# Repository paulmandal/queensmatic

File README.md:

# Queensmatic

This project is a wall-mounted NAS with controllable LED strips attached to its case.

# Requirements

- [Python](https://www.python.org/downloads/)
- [Docker CE](https://www.docker.com/community-edition#/download)
- [Android Studio + SDK](https://developer.android.com/studio/index.html)
- [Arduino](https://www.arduino.cc/en/Main/Software)
- [Eagle](https://www.autodesk.com/products/eagle/free-download)

# Table of Contents

| Directory | Contents |
|---|----|
| QueensmaticLEDController | Android LED controller application with simple color picker and touchscreen LED updating |
| hardware/circuit | Eagle schematics for the LED controller PCB |
| led-controller-uservice | Microservice used for communication between the Android app (or apps) and the LED controller hardware |
| ucontroller | Microcontroller code - receives messages from the API via serial and updates the LED strips |
| pictures | Some pictures of the building process |

# Running the API

```
cd led-controller-uservice
virtualenv venv
source venv/bin/activate
pip install docker-compose
# Update docker-compose.yml with the serial port for your microcontroller board -- under "devices"
docker-compose up
```

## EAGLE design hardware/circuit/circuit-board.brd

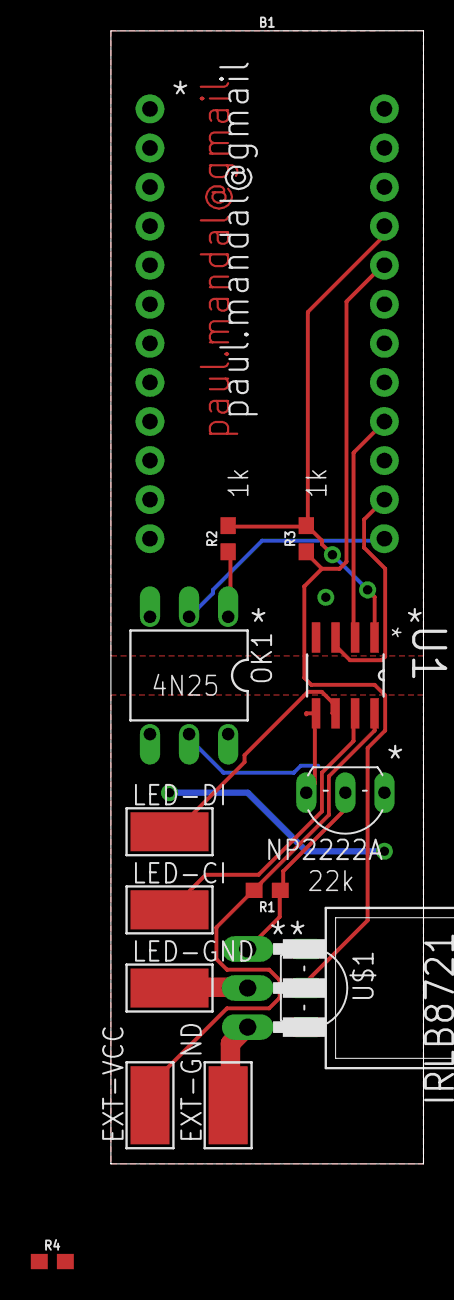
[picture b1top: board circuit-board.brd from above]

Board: 2 copper layers, 20.3 x 73.7 mm, 15 parts (0 on the bottom side), 15 nets.

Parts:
B1: SPARKFUN_PRO_MICRO
EXT-GND: WIREPADSMD5-2,5; 5-2,5
EXT-VCC: WIREPADSMD5-2,5; 5-2,5
IRLB8721: TO220BH
LED-CI: WIREPADSMD5-2,5; 5-2,5
LED-DI: WIREPADSMD5-2,5; 5-2,5
LED-GND: WIREPADSMD5-2,5; 5-2,5
NP2222A: 2N2222; TO92-EBC-OVAL
OK1: 4N25M; DIL06
R1: 22k; 0603
R2, R3: 1k; 0603
R4: 100k; 0603
U1: ADUM1200CRZ; SOIC127P600X175-8N
U$1: LM335AZ; TO92-

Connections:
+5V: EXT-VCC.1, R1.2, U1.8
ADUM-GND2: NP2222A.C, U1.5
GND: B1.3, B1.4, B1.23, U1.4, U$1.1
GNDA: EXT-GND.1, IRLB8721.S, NP2222A.E, OK1.4
unnamed: LED-DI.1, U1.6
unnamed: NP2222A.B, R4.2
unnamed: IRLB8721.D, LED-GND.1
unnamed: OK1.1, R2.1
unnamed: B1.14, U1.3
unnamed: B1.16, U1.2
unnamed: LED-CI.1, U1.7
unnamed: B1.13, OK1.2
PWR-CTRL: IRLB8721.G, OK1.5, R1.1, R4.1
TEMP: B1.20, R3.1, U$1.2
VCC: B1.21, R2.2, R3.2, U1.1

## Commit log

2017-03-11 Added WORKLIST.md to track tasks
2017-03-11 Added some possible improvements to IMPROVEMENTS.md
2017-03-11 Added API definition from SwaggerHub
2017-03-11 Added database definition to docs
2017-03-11 Added .gitignore files
2017-03-11 Added Flask setup, /configuration endpoint with GET, and initial configuration database creation
2017-03-11 Moved configuration database code into its own file, updated .gitignore
2017-03-12 configdb.py - added code to retrieve column names and to store updated configurations
2017-03-12 Added /configuration and /leds endpoints, added ucontroller.py to send update LED commands to the uController, added constants.py, Added /configuration and /leds endpoints for updating the config and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
2017-03-12 Added code to ucontroller.py to set the configuration on the uController, refactored a bit
2017-03-12 Refactore a bunch of names in API code
2017-03-12 Finished API for now, starting on uController code
2017-03-12 Set theme jekyll-theme-midnight
2017-03-12 Fixed an issues with ucontroller.set_config()
2017-03-12 Fixed an issue with update_led()
2017-03-12 Added uController skeleton, taking a break
2017-03-12 Added uController skeleton, added some improvements to improvements list
2017-03-12 Added uController commands documentation
2017-03-12 Added message buffer, handling of config update commands to uController code
2017-03-12 Added code to handle updating LEDs from serial commands, added code to output LED status to serial, added some comments,
2017-03-13 Renamed led_controller.ino to ucontroller.ino
2017-03-13 Added code to update LED strip to uController - need to debug LED protocol
2017-03-14 Changed r/g/b/brightness types to byte, normalized brightness value, fixed issue with headerByte not being reset before each LED loop, fixed issue with headerByte using & instead of |, added some deb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
2017-03-14 Removed debugging code, set up controller to update LED strip whenever configuration is changed
2017-03-14 Removed app->hardware r/g/b/brightness level remapping because most phones and LED strips only support 8-bit color
2017-03-14 Added Android app, created some data model objects
2017-03-15 Fleshed out config activity a bit, taking a break to eat
2017-03-15 Added fetching of configuration from API, set up Flask to listen to any interface
2017-03-15 Added storing of configuration from app->API, added permissions requesting, fixed JSON responses from API
2017-03-15 Moved JSON<->Native translation to ApiTranslator
2017-03-15 Added test button & LED updating to ApiConnection
2017-03-15 Fixed serial communication in Python code
2017-03-16 Started implementing LED drawing screen, added config fetching from API
2017-03-16 Finished setting up UI, setting up LED data structs now
2017-03-16 Basic drawing is in place - need to improve touch handling, right now you have to tap each LED but dragging the color over them would be a lot cooler
2017-03-16 Updated WORKLIST
2017-03-18 Added touch detection to drawing screen, it's in good enough shape for now, time to switch to hardware for a bit..
2017-03-18 Improved error handling in draw screen - user now has the option to re-try fetching the config, or they can cancel and go back to setup
2017-03-21 Added initial circuit diagram with just components
2017-03-21 Added wiring and some resistor values, replaced ISO7221MDR with ADUM1285CRZ because it has the pin arrangement (both inputs on the same side)
2017-03-21 Added temperature sensor to circuit schematic
2017-03-21 Added power pin toggling control to uController code
2017-03-21 Added status request to uController code, updated command docs
2017-03-22 Rerouted wiring for 4N25 optocoupler - signal was being inverted
2017-03-23 Added temperature sensor reading to uController code, added automatic poweroff above 40C
2017-03-23 Updated API definition to include /status endpoint, added GET/PUT, added get_status to API code
2017-03-23 Added PUT to /status endpoint, wired up to P command in uController
2017-03-23 Fixed incorrect pin assignment in LM335AZ in circuit schematic
2017-03-26 Fixed unit in uController code
2017-03-26 Added code to re-update LED strip after power is switched back on - strip loses its state when power is cut
2017-03-26 Added PN2222A to circuit - disconnects GND2 from ADUM1285CRZ so that current won't leak through the signal lines from the LED strip (LED strip wouldn't power off)
2017-03-26 Finished prototyping board
2017-03-26 Added pictures of testing SPI communication circuit
2017-03-26 Added picture from testing power switch signal output
2017-03-26 Added picture of testing optoisolator and N-channel MOSFET
2017-03-26 Added picture from testing LM335A temperature sensor
2017-03-26 Added picture from testing ADUM1285CRZ digital isolator
2017-03-26 Added picture from testing PN2222A N-channel transistor (power control for ADUM1285CRZ)
2017-03-26 Added picture from testing external power supply - circuit testing done!
2017-03-26 Added solder pads to circuit schematic
2017-03-27 Replaced power/signal holes with SMD pads, added initial PCB layout, changed pins for final board
2017-03-27 Added autorouted routes, thickened GND-A (LED ground thru MOSFET) traces, this will probably do, will run through DRUs and send it out tomorrow
2017-03-27 Added to PCB layout - added ground layers, some labels
2017-03-31 Finished circuit board layout, generating Gerber files now
2017-03-31 Generated Gerber files, sent off to PCB shop, now waiting begins..
2017-04-01 Added fetching of system status to ApiConnection, added ApiTranslator.systemStatusFromJson(JSONObject), added SystemStatus class
2017-04-01 Removed extra newlines after JavaDocs
2017-04-01 Added Power and MOSFET Temperature Status update to DrawingActivity, fixed some layout, added celsius string to strings.xml, added SystemStatusWorker to fetch system status updates
2017-04-01 Added error stack traces to ApiConnection
2017-04-01 Updated USB serial device name for new hardware, fixed datatype in for mosfet_temperature
2017-04-01 Added code to send power switch updates to the LED API
2017-04-01 Renamed some variables in LED API
2017-04-01 Cleaned up Android app code a bit
2017-04-01 Removed redundant system status listener interface
2017-04-01 First round of refactoring for uController code
2017-04-01 Moved Power & temperature control into HardwareController
2017-04-02 More refactoring, fixed issues where LEDs wouldn't update
2017-04-02 Added code to the Android app to reduce the number of LED updates sent to the API
2017-04-02 Moved Serial.begin() statement in uController code
2017-04-02 Fixed parsing of configuration empty strings
2017-04-02 Fixed powerState reading in LED API
2017-04-02 Updated worklist, more hardware times.. Ran into a weird issue - MOSFET might not be turning fully on? will need to read up and debug, hopefully this can be made to work with my existing circuit desi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
2017-04-02 Small morning refactors of uController code
2017-04-02 Updated worklist and list of improvements
2017-04-09 Cleaned up some constants in uController code
2017-04-09 Added missing 100k resistor to base of PN2222A, deleted flawed Gerber files - board layout is not updated for now because I have V2 in mind and PCBs in hand already
2017-04-12 Fixed an issue with touch detection - view coordinates for boundary rectangles were relative to their layout instead of the screen
2017-04-15 Updated improvements list
2017-04-15 Finished PCB from OSHPark
2017-04-15 First round of soldering on the PCB
2017-04-15 PCB fully populated
2017-04-15 Small 'patch' for a missing resistor - luckily this mistake didn't mean a new board order
2017-04-15 Removed delay() call from uController loop()
2017-04-15 Updated WORKLIST.md
2017-04-15 Renamed directory, added Dockerfile
2017-04-15 Added pyserial to requirements.txt
2017-04-16 Removed fullscreen from DrawingActivity - dragging on the screen would open the status bar too much
2017-04-16 Switched interpreter to Python 3.5, fixed an issue with regex pattern w/ pyserial in 3.5
2017-04-16 Updated WORKLIST and added api testing script, something is not updating fast enough, it might be good to pool updates - update the strip regularly (if changed) every 10ms or something instead of let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
2017-05-08 Added twinkle.py to test uController - turns out repeatedly opening and closing the serial connection doesn't cause issues with slow updates, updating API code
2017-05-08 Reworked API code to open and close serial port for each transmission
2017-05-08 Fixed an issue where power state was not being read correctly
2017-05-08 Increased size of drawable strip areas, lots of touch events weren't hitting the drawable areas before
2017-05-08 Updated default LED count in led_controller.cpp and configdb.py
2017-05-08 Fixed layout direction for bottom LED strip in app - LEDs updating in reverse on the physical strip
2017-07-08 Updated worklist, added picture of NAS construction
2017-07-08 Added picture of frame-fitting
2017-07-08 Added picture of frame construction
2017-07-08 Added picture from verifying the frame fit correctly
2017-07-08 Added picture of test mounts on scrap wood
2017-07-08 Added pictures of templates for HDDs + mobo (these ended up not being used)
2017-07-08 Added picture of cutting holes in backboard
2017-07-08 Added various measurement calculations scratch work
2017-07-08 Added picture of gluing down LED strips
2017-07-08 Added picture of "kinda" final build
2017-07-08 Fixed layout orientation for lefthand LED strip
2017-07-08 Added default values == actual LED lenghts for our hardware
2017-07-08 Updated LED uController code with default LED size -- still fiddling with hardware (some of the strip is not lighting some of the time)
2017-07-12 Updated config db with actual values
2017-07-12 Added picture of taped up back
2017-07-12 Added detail picture of LED strip mount
2017-07-12 Added picture of finished frame
2017-07-12 Added picture of finished frame with LED strips lit up purple
2017-07-15 Renamed py3.5 -> venv
2017-07-15 Added docker-compose to requirements.txt, locked in versions for all libs
2017-07-15 Remove docker-compose from requirements.txt since it's not part of the application
2017-07-15 Added docker-compose.yml
2017-07-15 Deleted run-container.sh
2017-07-15 Updated ucontroller python virtualenv to be venv
2017-07-15 Added README.md
2017-07-15 lolwhy
2017-07-15 Updated README.md to remove unnecessary dependencies
2017-07-15 Removed extra Icebox in WORKLIST.md

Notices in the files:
parts and their libraries:
SparkFun-Boards: Licensing: Creative Commons ShareAlike 4.0 International - https://creativecommons.org/licenses/by-sa/4.0
